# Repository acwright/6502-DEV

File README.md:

6502-DEV
========

An **AC6502** retro-style 8-bit computer based on the **65C02** microprocessor.

> 📖 **Guide:** [AC6502 Documentation](https://acwright.github.io/6502-DOCS/) — the user's and programmer's guide for the whole family.
> See [DEV's page in the family appendix](https://acwright.github.io/6502-DOCS/family/dev).

---

**Building one? Every part you need, with supplier numbers and known issues, is in [BOM.md](BOM.md).**

## Table of Contents

- [Overview](#overview)
- [Architecture](#architecture)
- [Systems](#systems)
- [Software](#software)
- [Hardware](#hardware)
  - [DEV Board](#dev-board)
  - [DEV Output Board](#dev-output-board)
- [Which revision to make](#which-revision-to-make)
- [Firmware](#firmware)
  - [DB Emulator](#db-emulator)
  - [DOB Display](#dob-display)
- [CAD](#cad)
- [Production](#production)
- [Schematics](#schematics)
- [Shared lines](#shared-lines)
- [Extra pins: `EXP0`–`EXP3` and `HRDB`](#extra-pins-exp0exp3-and-hrdb)
- [Jumpers](#jumpers)
- [Off-board headers](#off-board-headers)
- [Libraries](#libraries)
- [Bill of Materials](#bill-of-materials)
- [License](#license)

---

## Overview

The AC6502 ecosystem is a family of open-source, 65C02-based computers sharing a common architecture, memory map, and [BIOS](https://github.com/acwright/6502-BIOS). Each computer in the family is purpose-built for a different use case but runs the same software and firmware.

The **DEV** is an emulation-based development system. It replaces the physical 65C02 CPU with a [Teensy 4.1](https://www.pjrc.com/store/teensy41.html) running cycle-accurate 65C02 emulation via [vrEmu6502](https://github.com/visrealm/vrEmu6502).
## Architecture

All AC6502 computers share:

- **CPU**: 65C02 (or accurate emulation)
- **Memory**: 32KB RAM + 32KB ROM, with optional banked RAM expansion
- **Memory Map**: Standardized across the ecosystem — zero page, stack, I/O space ($8000–$9FFF), system ROM, and interrupt vectors at $FFFA–$FFFF
- **Bus**: 16-bit address bus, 8-bit bidirectional data bus, standard 65C02 control signals (RW, PHI2, RESET, IRQ, NMI, RDY, SYNC)
- **BIOS**: A common [BIOS](https://github.com/acwright/6502-BIOS) provides the kernel, monitor, and BASIC interpreter across all systems

## Systems

| Project | Description |
|---------|-------------|
| [6502-ACE](https://github.com/acwright/6502-ACE) | All-in-one Computer Experience — A single board computer |
| [6502-COB](https://github.com/acwright/6502-COB) | Computer On a Backplane — Modular desktop computer with expandable card slots |
| [6502-DEV](https://github.com/acwright/6502-DEV) | Development Environment Vehicle — Emulation-based dev system (YOU ARE HERE) |
| [6502-KIM](https://github.com/acwright/6502-KIM) | Keypad Input Monitor - KIM-1 inspired minimal computer |
| [6502-VCS](https://github.com/acwright/6502-VCS) | Video Computer System — Cartridge-based retro gaming console |

## Software

| Project | Description |
|---------|-------------|
| [6502-BIOS](https://github.com/acwright/6502-BIOS) | The shared BIOS (kernel, monitor, BASIC) for all AC6502 computers |
| [6502-EMULATOR](https://github.com/acwright/6502-EMULATOR) | Emulator for the whole family — desktop app, browser build, and a command line for scripted runs |
| [6502-PRG](https://github.com/acwright/6502-PRG) | Template project for writing assembly language programs |
| [6502-CRT](https://github.com/acwright/6502-CRT) | Template project for writing assembly language cartridges |
| [6502-ASM](https://github.com/acwright/6502-ASM) | Assembly language example programs and demos |
| [6502-BAS](https://github.com/acwright/6502-BAS) | BASIC program listings |
| [6502-WOZMON](https://github.com/acwright/6502-WOZMON) | Wozmon as a standalone ROM |
| [6502-NOP](https://github.com/acwright/6502-NOP) | An all-NOP ROM, for probing a board during bring-up |
| [6502-DOCS](https://github.com/acwright/6502-DOCS) | The documentation site — the guide, the printable reference cards, branding and label artwork |
| [cffs](https://github.com/acwright/cffs) | Builds CompactFlash disk images for the BIOS filesystem |
| [bastok](https://github.com/acwright/bastok) | Tokenizes BASIC listings into `.prg` images, and back |
| [bin2woz](https://github.com/acwright/bin2woz) | Converts a binary into a Wozmon serial upload |

## Hardware

This repository contains KiCad 7.0+ PCB designs for the two boards that make up the DEV system.

### DEV Board
`Hardware/DEV Board/`

The main board hosting the Teensy 4.1. Provides 65C02 bus emulation, SD card storage, Ethernet, USB keyboard/joystick input, and hardware control buttons (Run/Stop, Step, Reset, Frequency). Includes a bus connector and card slot with level shifters for optional real hardware expansion.

### DEV Output Board
`Hardware/DEV Output Board/`

The AV output board hosting a Teensy 4.0 and a 2.4" ILI9341 TFT LCD. Emulates a TMS9918A Video Display Processor and a MOS 6581 SID audio synthesizer, driven in real time via high-speed serial from the DEV Board. The DEV Board sends the same AV packets over USB at the same time, so a browser can render the output in parallel with this board — the two paths are simultaneous, not alternatives.

<!-- Which revision to make: generated by Tools/revision-audit/register.py from Tools/data/orders.json. Edit that file, not this section. -->
## Which revision to make

**Make the newest revision of a board, and check its label first.** The table below gives each board's newest revision. A newer revision fixes what was found on the older ones. Every revision, old and new, is in [REVISIONS.md](REVISIONS.md), with what changed in each.

Each revision carries one of three labels:

- **Tested:** This revision was built and tested.
- **Proven design:** Not built at this revision, but its circuit is a tested revision's. The only changes are silkscreen text, part values, mounting holes, outline clean-up, parts moved a fraction of a millimetre onto their grid, capacitor pitch, socket outlines, a footprint swap with the same holes, a solder jumper's default, the solder mask or paste at a card edge, or tracks rerouted or pours refilled with DRC and the netlist check passing. A builder can treat it as tested.
- **Untested:** The circuit, the power path or the layout changed in a way that only a built board proves, or the board has never been built at all.

[BOM.md](BOM.md) has the parts for every revision, and its known issues.

| Board | Newest revision | Label | Why |
|---|---|---|---|
| DEV Board | 1.1 | **Proven design** | Rev 1.0's circuit; the IC designators placed by the family's rule. |
| DEV Output Board | 1.1 | **Proven design** | Silkscreen text only. |
<!-- End of which revision to make -->

## Firmware

This repository contains [PlatformIO](https://platformio.org/)-based firmware for both boards.

### DB Emulator
`Firmware/DB Emulator/`

Firmware for the Teensy 4.1 on the DEV Board. Provides:

- Cycle-accurate 65C02 emulation
- SD card ROM/cartridge/program loading and memory snapshots
- Ethernet with mDNS (`6502.local`) and an embedded web control interface
- USB keyboard and joystick support (Xbox 360/One)
- AV packet output to both destinations at once — over USB to the browser (Web Serial API) and over hardware UART at 6 Mbps to the DOB Display
- Serial terminal interface (115200 baud)
- Hardware button control (Run/Stop, Step, Reset, Frequency)
- Variable CPU clock speed

See [Firmware/DB Emulator/README.md](./Firmware/DB%20Emulator/README.md) for setup and usage instructions.

### DOB Display
`Firmware/DOB Display/`

Firmware for the Teensy 4.0 on the DEV Output Board. Provides:

- TMS9918A VDP emulation (all four display modes, 256×192 active area)
- MOS 6581 SID audio emulation (3 voices, ADSR envelopes, PWM audio output)
- AV packet stream input at 6 Mbps over hardware UART from the DB Emulator (which also streams the same packets over USB to the browser)

See [Firmware/DOB Display/README.md](./Firmware/DOB%20Display/README.md) for setup and usage instructions.

## CAD
`CAD/`

3D-printable enclosure parts and laser-cut top panels for the DEV system.

**Board images** are in `CAD/Images/<Board>/Rev X/`: `Front.png` and `Back.png` on white, and `Front Transparent.png` and `Back Transparent.png` with no background. Every image is a 3D render at the same size, with the black solder mask and white silkscreen the boards are made with. Bare-board photos may differ, because the renders show parts fitted.

**Top panels are versioned by board revision**, like `Hardware/`: `CAD/Tops/<Board>/Rev X/`. Each revision has its own complete folder, even when two revisions share the same files. `Bases/` holds the parts for a whole computer, not for one board, so it isn't versioned.

The **[plate mounting drawing](CAD/Bases/Plate%20Mounting%20Drawing.png)** ([SVG](CAD/Bases/Plate%20Mounting%20Drawing.svg)) shows where the DEV Board and the DEV Output Board mount on the base plate, with every hole's position and the hardware the build needs. The plate is a stack of three 3 mm acrylic layers.

## Production
`Production/`

[REVISIONS.md](REVISIONS.md) lists every board revision: whether it was made, its JLCPCB order, the commit it was made from, and what fits it.

JLCPCB-ready Gerber files and BOM/CPL for PCB fabrication and assembly.

## Schematics
`Schematics/`

PDF schematics for each board.

## Shared lines

Five lines of the 6502 bus are shared by every board on it: `RESB`, `IRQB`, `NMIB`, `RDY` and `BE`. A board may pull one of these lines low, and nothing drives one high. Each line is held high by one 10kΩ pull-up resistor to VCC, on the board with the CPU: the ACE Board, the KIM Board, the VCS Main Board, the COB CPU Card or CPU Card Pro, or the DEV Board. No other board has one. Two pull-ups on the same line would sit in parallel and lower its resistance, so a card that adds its own pull-up changes the machine for every other board. The VIAs and PIAs in the BOMs, the W65C22N and W65C21N, have open-drain interrupt outputs for this reason.

**Interrupt outputs.** Whatever drives `IRQB` or `NMIB` may only pull it low. Every board is drawn for the parts in its BOM and works as shipped, with no jumper to cut or bridge:

- **A part whose interrupt output is open-drain** (the W65C22N, W65C21N, R6551AP, DS1511Y and TMS9918A) drives the line directly, or through a diode with a solder jumper across it that ships bridged. The diode is fitted either way. To use a part that drives its interrupt high as well as low instead, such as a W65C22S or a replacement of your own, cut the jumper: the diode then lets the part only pull the line low. A board with no diode in the line can't take such a part.
- **A part that drives its interrupt high as well as low** (the pico9918, the VERA module, and a microcontroller such as the ATmega1284 or a Raspberry Pi Pico) reaches the line through a diode, a BAT85 or a 1N914, with its cathode toward the part. Where a solder jumper sits across that diode, it ships open. The diode is then the only path to the line, so fit it, and never bridge the jumper, because the part would then hold the line high against every other interrupt source.
- **A microcontroller wired to the line directly,** as on the ACE Board, the Mega Helper and the Flash Helper, drives it open-drain in its firmware: it sets the pin low or leaves it as an input, and never drives it high.

The *Jumpers* section below gives each board's interrupt jumper.

The same holds where a board has its own reset circuit. A reset switch, its timer and the transistor that pulls `RESB` low can be on any board, such as the COB Backplane Pro or the Clock Card, but the `RESB` pull-up is only ever on the board with the CPU. Each of those boards draws its pull-ups together, in one group on its schematic.

The DEV Board is the exception on `RESB`. It stands in for a Main Board, so it owns reset: its Reset button goes to the Teensy, and the Teensy drives `RESB` onto the bus through U3, a level shifter that only sends signals out, as it drives `PHI2`. U3 holds `RESB` high or low, so the DEV Board has no `RESB` pull-up, and nothing else on its bus may pull `RESB` low. Connect a DEV only to a passive backplane, never to the COB Backplane Pro, whose reset circuit would pull against U3, and don't fit a card that pulls `RESB` low, such as the COB RTC Card.

`SOB` is a CPU pin that isn't on the bus. It is tied to VCC, directly or through a 10kΩ resistor.

A few chips have a pull-up of their own inside the chip, such as an ATmega's reset pin. Where such a pin is wired to `RESB`, its pull-up of 30–60kΩ sits in parallel with the 10kΩ one. That's harmless, because whatever pulls `RESB` low can sink the extra current many times over.

A revision that doesn't follow this yet says so in its known issues in [BOM.md](BOM.md), with what to fit or remove.

## Extra pins: `EXP0`–`EXP3` and `HRDB`

`EXP` stands for "extra pin". Four pins of the 6502 bus are left for a builder's own use: pin 4 is `EXP1`, pin 6 is `EXP0`, pin 19 is `EXP3` and pin 21 is `EXP2`.

Pins 4 and 6 have a second job. A cartridge ties both of them to GND. That pulls `HRDB` ("High ROM disable bar", active low) low on the board with the ROM, which takes `$C000–$FFFF` away from the ROM so that the cartridge answers there instead. So in a build that uses cartridges, pins 4 and 6 are reserved for `HRDB`, and nothing else may drive them. They are free as `EXP1` and `EXP0` only in a build that never uses cartridges. `EXP2` and `EXP3` are always free.

How the boards treat pins 4 and 6:

- **The ACE Board and the KIM Board** join them to their ROM's `HRDB` input, and their silk says `HRDB`. The VCS Main Board joins them the same way from Rev 1.1.
- **The COB Memory Card** joins them to its `HRDB` only through jumpers: fit two shunts on J2, or bridge JP1 and JP2, in a COB that takes cartridges. It is the only board with these jumpers, because the COB is the experimenter's build. The VCS Main Board Rev 1.0 had them too (J5, or JP3 and JP4); fit them, because the VCS always takes cartridges.
- **A cartridge** (the ROM Cart, the Flash Cart, the KIM Keypad Card) ties them to GND.
- **A board that only carries the bus through**, such as a backplane or a helper, calls them `EXP1` and `EXP0`, as its silk does, and a note on its schematic says what they carry.

<!-- Jumpers: generated by Tools/jumpers/gen.py from Tools/data/jumpers.json. Edit that file, not this section. -->
## Jumpers

None of this repository's boards has a jumper.

<!-- End of jumpers -->

<!-- Off-board headers: generated by Tools/offboard/gen.py from Tools/offboard/offboard.json, Tools/data/offboard.json and the PCB files. Edit those, not this section. -->
## Off-board headers

Some boards have small headers, such as `RESET SW`, `CLOCK ENBL SW`, `POWER LED` and `VCC`, that a standard build leaves empty. They are for a machine built into a full enclosure, which AC6502 doesn't offer today. In such a build, the parts a person handles are mounted on the case and wired to the board through these headers: the power jack, the switches, the LEDs and the keyboard. The matching parts on the board are then left off. For example, an ACE Board can sit inside a case with its power jack, power switch and key switches left off, and a Keyboard Helper as its keyboard.

To build a board for a case:

1. Fit the header, and wire the part on the case to it. The table says what goes on each pin.
2. Leave off the parts on the board that the table names. A button on the case can work beside the board's own button, but some parts, such as an LED that shares the board's resistor, can't share.
3. Set any jumper the table mentions. The [Jumpers](#jumpers) section has the rest.

The connector follows the kind of build. A single-board machine, the ACE Board or the KIM Board, uses plain 2.54 mm pin headers, which are simpler and cheaper. A board in a multi-board machine, every COB board and the separate boards of the VCS, the DEV and the KIM, uses JST XH, the family's standard for these headers.

The table lists every off-board header on each board's newest revision, read from the board's PCB file.

| Board | Rev | Header | Label | Connector | What it's for | Leave off |
|---|---|---|---|---|---|---|
| DEV Board | 1.1 | J3 | `PANEL` | Pin header, 2×4, 2.54 mm | Four buttons on the case, each between its pin and ground: Run/Stop on pin 1, Step on pin 3, Clock on pin 5 and Reset on pin 7. Pins 2, 4, 6 and 8 are ground. Each button is wired across one of SW1–SW4, the board's own buttons. | SW1–SW4, if the case covers them. Both sets of buttons work if they stay. |

<!-- End of off-board headers -->

## Libraries
`Libraries/`

Shared KiCad symbol and footprint libraries used across all AC6502 hardware projects, with their 3D models in `Models/`. A part is named for what it is and its shape, such as `RJ45 Jack LED` or `CR2032 Holder`, never for a manufacturer's part number, so a replacement part with the same footprint fits without renaming anything. The part numbers to buy are in [BOM.md](BOM.md). Every AC6502 repository carries the same copy of each part.

## Bill of Materials

Every part for every board, by revision, is in **[BOM.md](BOM.md)**, with supplier numbers, known issues, build notes and files to upload to Digi-Key and Mouser. What changed in each revision, and what is known about each one, is in **[REVISIONS.md](REVISIONS.md)**.

## License

Hardware designs are released under the [CERN Open Hardware Licence Version 2 – Permissive](https://ohwr.org/cern_ohl_p_v2.txt).  
Firmware is released under the MIT License — [DB Emulator](./Firmware/DB%20Emulator/LICENSE), [DOB Display](./Firmware/DOB%20Display/LICENSE).

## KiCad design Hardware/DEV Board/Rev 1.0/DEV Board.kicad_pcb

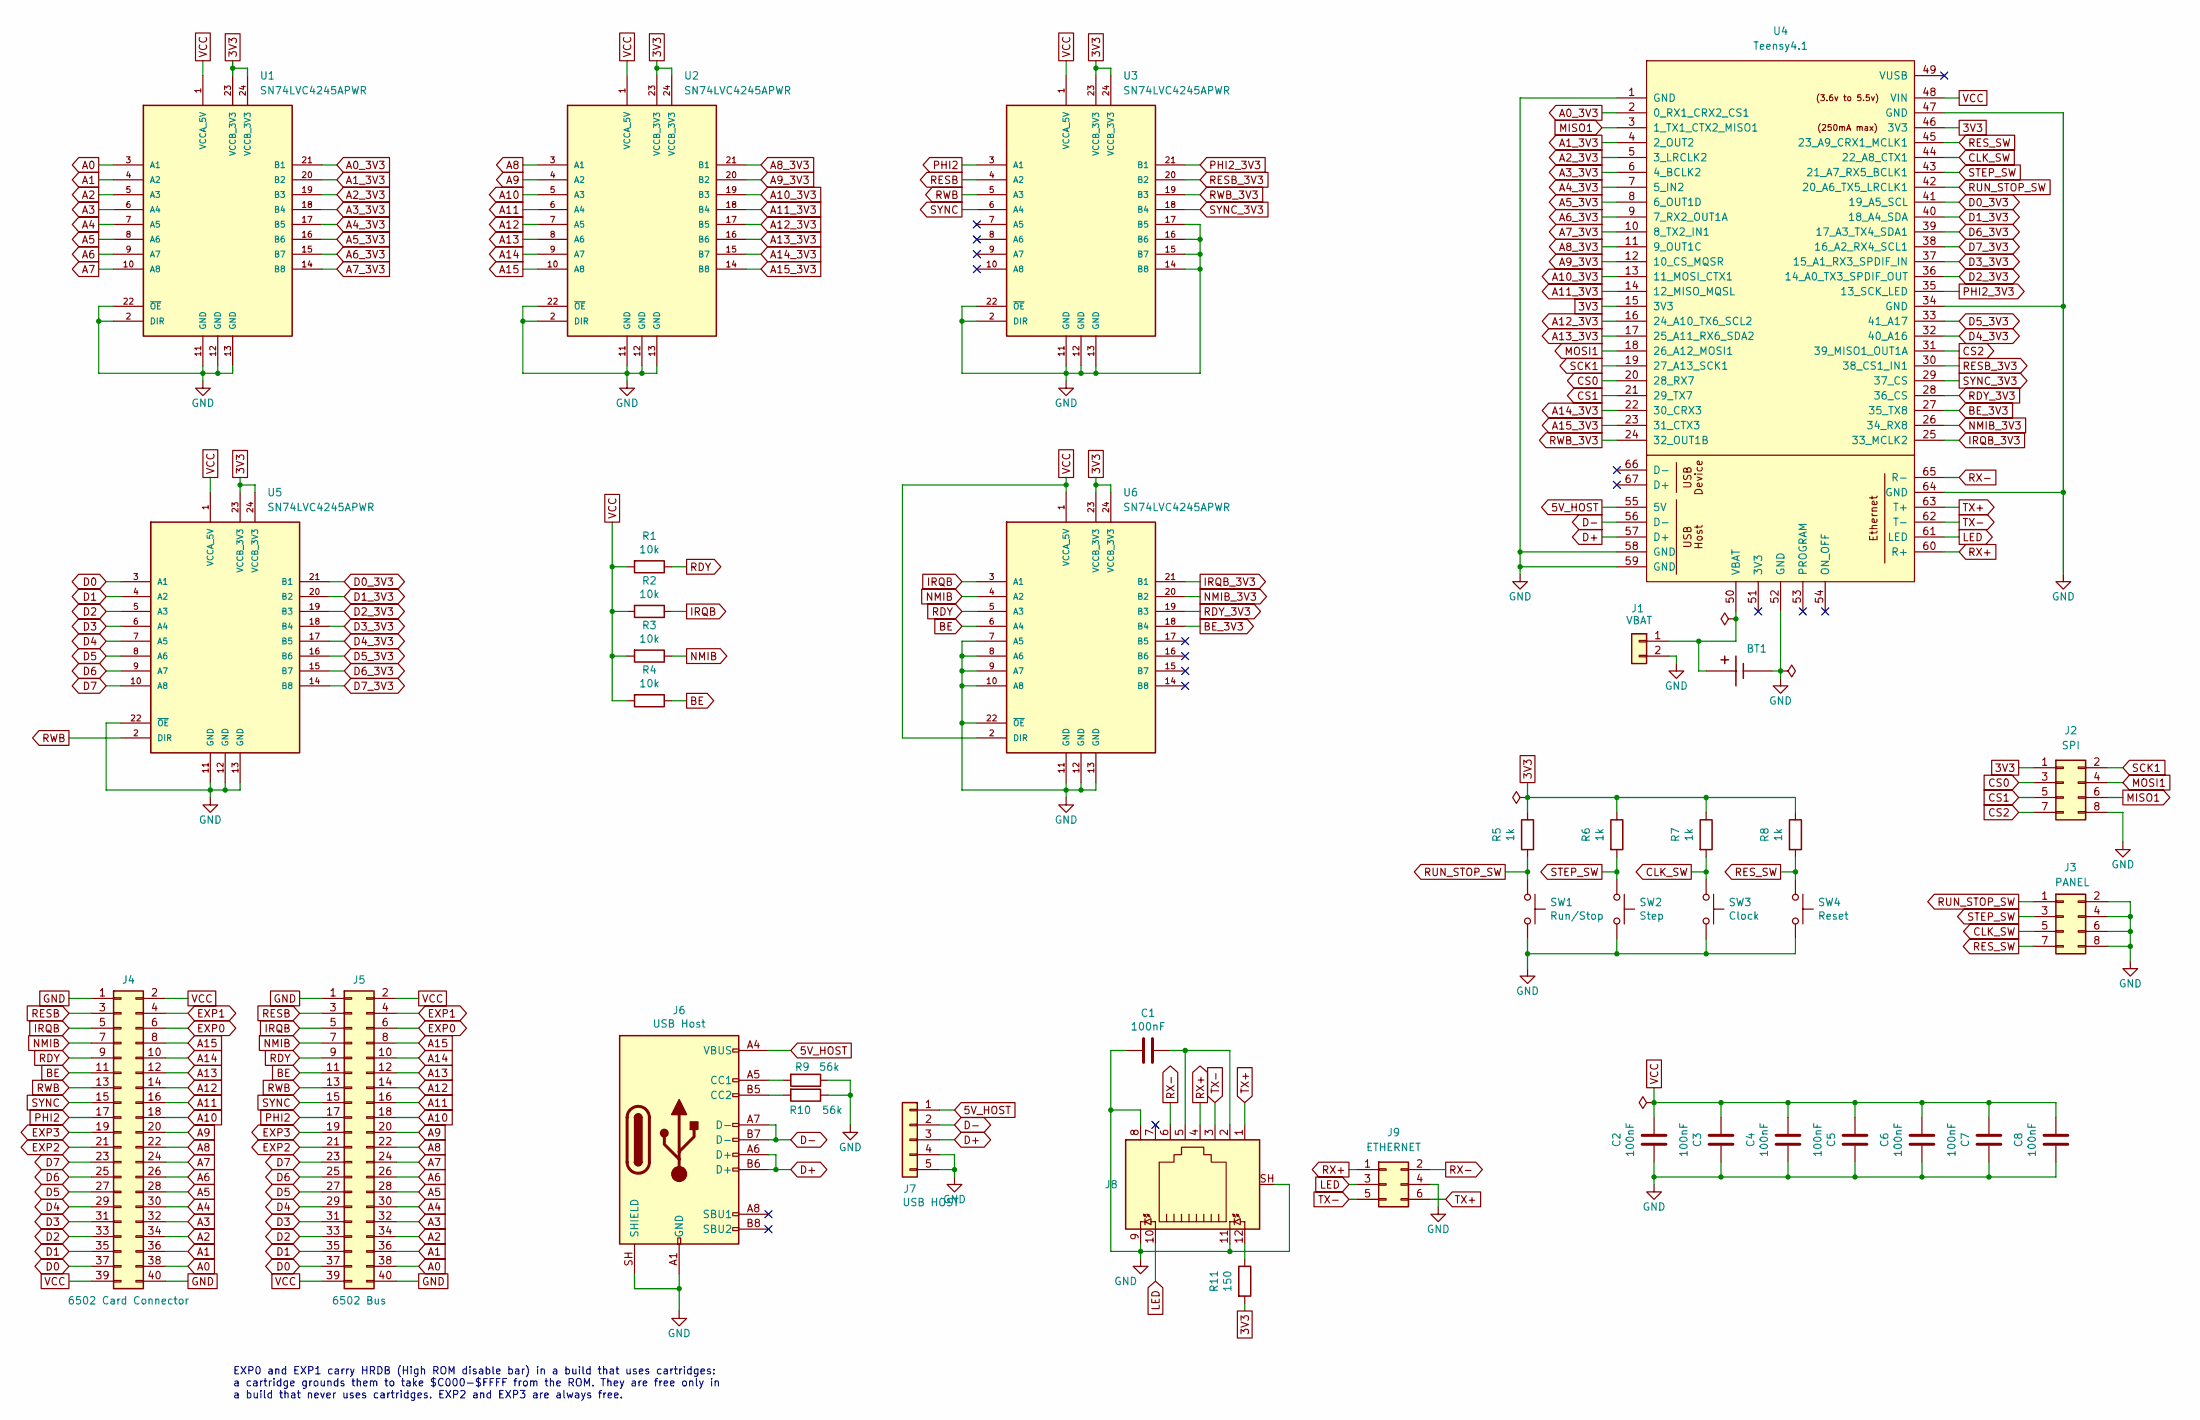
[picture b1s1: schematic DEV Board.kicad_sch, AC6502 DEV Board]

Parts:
BT1: CR2032; CR2032 Holder; Digikey 343-BAT-HLD-001-THM-TRCT-ND
C1, C2, C3, C4, C5, C6, C7, C8: 100nF; C_0805_2012Metric; LCSC C49678
J1: VBAT; PinHeader_1x02_P2.54mm_Vertical; Digikey S1011EC-40-ND
J2: SPI; PinHeader_2x04_P2.54mm_Vertical; Digikey S2011EC-40-ND
J3: PANEL; PinHeader_2x04_P2.54mm_Vertical; Digikey S2011EC-40-ND
J4: 6502 Card Connector; 6502 Card Slot; Digikey A31723-ND
J5: 6502 Bus; 6502 Bus Connector; Digikey 732-5401-ND
J6: USB Host; USB_C_Receptacle_HRO_TYPE-C-31-M-12; LCSC C2988369
J7: USB HOST; PinHeader_1x05_P2.54mm_Vertical; Digikey S1011EC-40-ND
J8: RJ45_LED; RJ45 Jack LED; Digikey 931-TMJDD111B083FC2A1D-ND
J9: ETHERNET; PinHeader_2x03_P2.00mm_Vertical; Digikey 2057-2PH2-06-UA-ND
R1, R2, R3, R4: 10k; R_0805_2012Metric; LCSC C17414
R5, R6, R7, R8: 1k; R_0805_2012Metric; LCSC C17513
R9, R10: 56k; R_0805_2012Metric; LCSC C169923
R11: 150; R_0805_2012Metric; LCSC C17471
SW1: Run/Stop; Tact Switch SMD 5.1mm; LCSC C318884
SW2: Step; Tact Switch SMD 5.1mm; LCSC C318884
SW3: Clock; Tact Switch SMD 5.1mm; LCSC C318884
SW4: Reset; Tact Switch SMD 5.1mm; LCSC C318884
U1, U2, U3, U5, U6: SN74LVC4245APWR; TSSOP-24_4.4x7.8mm_P0.65mm; LCSC C7859
U4: Teensy4.1; Teensy41

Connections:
3V3: J2.1, R5.1, R6.1, R7.1, R8.1, R11.2, U1.23 (VCCB_3V3), U1.24 (VCCB_3V3), U2.23 (VCCB_3V3), U2.24 (VCCB_3V3), U3.23 (VCCB_3V3), U3.24 (VCCB_3V3), U4.15 (3V3), U4.46 (3V3), U5.23 (VCCB_3V3), U5.24 (VCCB_3V3), U6.23 (VCCB_3V3), U6.24 (VCCB_3V3)
5V_HOST: J6.A4 (VBUS), J6.A9 (VBUS), J6.B4 (VBUS), J6.B9 (VBUS), J7.1, U4.55 (5V)
A0: J4.38, J5.38, U1.3 (A1)
A0_3V3: U1.21 (B1), U4.2 (0_RX1_CRX2_CS1)
A1: J4.36, J5.36, U1.4 (A2)
A1_3V3: U1.20 (B2), U4.4 (2_OUT2)
A2: J4.34, J5.34, U1.5 (A3)
A2_3V3: U1.19 (B3), U4.5 (3_LRCLK2)
A3: J4.32, J5.32, U1.6 (A4)
A3_3V3: U1.18 (B4), U4.6 (4_BCLK2)
A4: J4.30, J5.30, U1.7 (A5)
A4_3V3: U1.17 (B5), U4.7 (5_IN2)
A5: J4.28, J5.28, U1.8 (A6)
A5_3V3: U1.16 (B6), U4.8 (6_OUT1D)
A6: J4.26, J5.26, U1.9 (A7)
A6_3V3: U1.15 (B7), U4.9 (7_RX2_OUT1A)
A7: J4.24, J5.24, U1.10 (A8)
A7_3V3: U1.14 (B8), U4.10 (8_TX2_IN1)
A8: J4.22, J5.22, U2.3 (A1)
A8_3V3: U2.21 (B1), U4.11 (9_OUT1C)
A9: J4.20, J5.20, U2.4 (A2)
A9_3V3: U2.20 (B2), U4.12 (10_CS_MQSR)
A10: J4.18, J5.18, U2.5 (A3)
A10_3V3: U2.19 (B3), U4.13 (11_MOSI_CTX1)
A11: J4.16, J5.16, U2.6 (A4)
A11_3V3: U2.18 (B4), U4.14 (12_MISO_MQSL)
A12: J4.14, J5.14, U2.7 (A5)
A12_3V3: U2.17 (B5), U4.16 (24_A10_TX6_SCL2)
A13: J4.12, J5.12, U2.8 (A6)
A13_3V3: U2.16 (B6), U4.17 (25_A11_RX6_SDA2)
A14: J4.10, J5.10, U2.9 (A7)
A14_3V3: U2.15 (B7), U4.22 (30_CRX3)
A15: J4.8, J5.8, U2.10 (A8)
A15_3V3: U2.14 (B8), U4.23 (31_CTX3)
BE: J4.11, J5.11, R4.1, U6.6 (A4)
BE_3V3: U4.27 (35_TX8), U6.18 (B4)
CLK_SW: J3.5, R7.2, SW3.1, U4.44 (22_A8_CTX1)
CS0: J2.3, U4.20 (28_RX7)
CS1: J2.5, U4.21 (29_TX7)
CS2: J2.7, U4.31 (39_MISO1_OUT1A)
D0: J4.37, J5.37, U5.3 (A1)
D0_3V3: U4.41 (19_A5_SCL), U5.21 (B1)
D1: J4.35, J5.35, U5.4 (A2)
D1_3V3: U4.40 (18_A4_SDA), U5.20 (B2)
D2: J4.33, J5.33, U5.5 (A3)
D2_3V3: U4.36 (14_A0_TX3_SPDIF_OUT), U5.19 (B3)
D3: J4.31, J5.31, U5.6 (A4)
D3_3V3: U4.37 (15_A1_RX3_SPDIF_IN), U5.18 (B4)
D4: J4.29, J5.29, U5.7 (A5)
D4_3V3: U4.32 (40_A16), U5.17 (B5)
D5: J4.27, J5.27, U5.8 (A6)
D5_3V3: U4.33 (41_A17), U5.16 (B6)
D6: J4.25, J5.25, U5.9 (A7)
D6_3V3: U4.39 (17_A3_TX4_SDA1), U5.15 (B7)
D7: J4.23, J5.23, U5.10 (A8)
D7_3V3: U4.38 (16_A2_RX4_SCL1), U5.14 (B8)
D+: J6.A6 (D+), J6.B6 (D+), J7.3, U4.57 (D+)
D-: J6.A7 (D-), J6.B7 (D-), J7.2, U4.56 (D-)
EXP0: J4.6, J5.6
EXP1: J4.4, J5.4
EXP2: J4.21, J5.21
EXP3: J4.19, J5.19
GND: BT1.-, C1.2, C2.2, C3.1, C4.2, C5.1, C6.2, C7.1, C8.2, J1.2, J2.8, J3.2, J3.4, J3.6, J3.8, J4.1, J4.40, J5.1, J5.40, J6.A1 (GND), J6.A12 (GND), J6.B1 (GND), J6.B12 (GND), J6.S1 (SHIELD), J6.SH (SHIELD), J7.4, J7.5, J8.8, J8.9, J8.11, J8.SH, J9.4, R9.1, R10.1, SW1.2, SW2.2, SW3.2, SW4.2, U1.2 (DIR), U1.11 (GND), U1.12 (GND), U1.13 (GND), U1.22 (~OE), U2.2 (DIR), U2.11 (GND), U2.12 (GND), U2.13 (GND), U2.22 (~OE), U3.2 (DIR), U3.11 (GND), U3.12 (GND), U3.13 (GND), U3.14 (B8), U3.15 (B7), U3.16 (B6), U3.17 (B5), U3.22 (~OE), U4.1 (GND), U4.34 (GND), U4.47 (GND), U4.52 (GND), U4.58 (GND), U4.59 (GND), U4.64 (GND), U5.11 (GND), U5.12 (GND), U5.13 (GND), U5.22 (~OE), U6.7 (A5), U6.8 (A6), U6.9 (A7), U6.10 (A8), U6.11 (GND), U6.12 (GND), U6.13 (GND), U6.22 (~OE)
IRQB: J4.5, J5.5, R2.1, U6.3 (A1)
IRQB_3V3: U4.25 (33_MCLK2), U6.21 (B1)
LED: J8.10, J9.3, U4.61 (LED)
MISO1: J2.6, U4.3 (1_TX1_CTX2_MISO1)
MOSI1: J2.4, U4.18 (26_A12_MOSI1)
NMIB: J4.7, J5.7, R3.1, U6.4 (A2)
NMIB_3V3: U4.26 (34_RX8), U6.20 (B2)
unnamed: C1.1, J8.2, J8.5
unnamed: BT1.+, J1.1, U4.50 (VBAT)
unnamed: J6.A5 (CC1), R9.2
unnamed: J6.B5 (CC2), R10.2
unnamed: J8.12, R11.1
PHI2: J4.17, J5.17, U3.3 (A1)
PHI2_3V3: U3.21 (B1), U4.35 (13_SCK_LED)
RDY: J4.9, J5.9, R1.1, U6.5 (A3)
RDY_3V3: U4.28 (36_CS), U6.19 (B3)
RESB: J4.3, J5.3, U3.4 (A2)
RESB_3V3: U3.20 (B2), U4.30 (38_CS1_IN1)
RES_SW: J3.7, R8.2, SW4.1, U4.45 (23_A9_CRX1_MCLK1)
RUN_STOP_SW: J3.1, R5.2, SW1.1, U4.42 (20_A6_TX5_LRCLK1)
RWB: J4.13, J5.13, U3.5 (A3), U5.2 (DIR)
RWB_3V3: U3.19 (B3), U4.24 (32_OUT1B)
RX+: J8.4, J9.1, U4.60 (R+)
RX-: J8.6, J9.2, U4.65 (R-)
SCK1: J2.2, U4.19 (27_A13_SCK1)
STEP_SW: J3.3, R6.2, SW2.1, U4.43 (21_A7_RX5_BCLK1)
SYNC: J4.15, J5.15, U3.6 (A4)
SYNC_3V3: U3.18 (B4), U4.29 (37_CS)
TX+: J8.1, J9.6, U4.63 (T+)
TX-: J8.3, J9.5, U4.62 (T-)
VCC: C2.1, C3.2, C4.1, C5.2, C6.1, C7.2, C8.1, J4.2, J4.39, J5.2, J5.39, R1.2, R2.2, R3.2, R4.2, U1.1 (VCCA_5V), U2.1 (VCCA_5V), U3.1 (VCCA_5V), U4.48 (VIN), U5.1 (VCCA_5V), U6.1 (VCCA_5V), U6.2 (DIR)

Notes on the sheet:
EXP0 and EXP1 carry HRDB (High ROM disable bar) in a build that uses cartridges: a cartridge grounds them to take $C000-$FFFF from the ROM. They are free only in a build that never uses cartridges. EXP2 and EXP3 are always free.

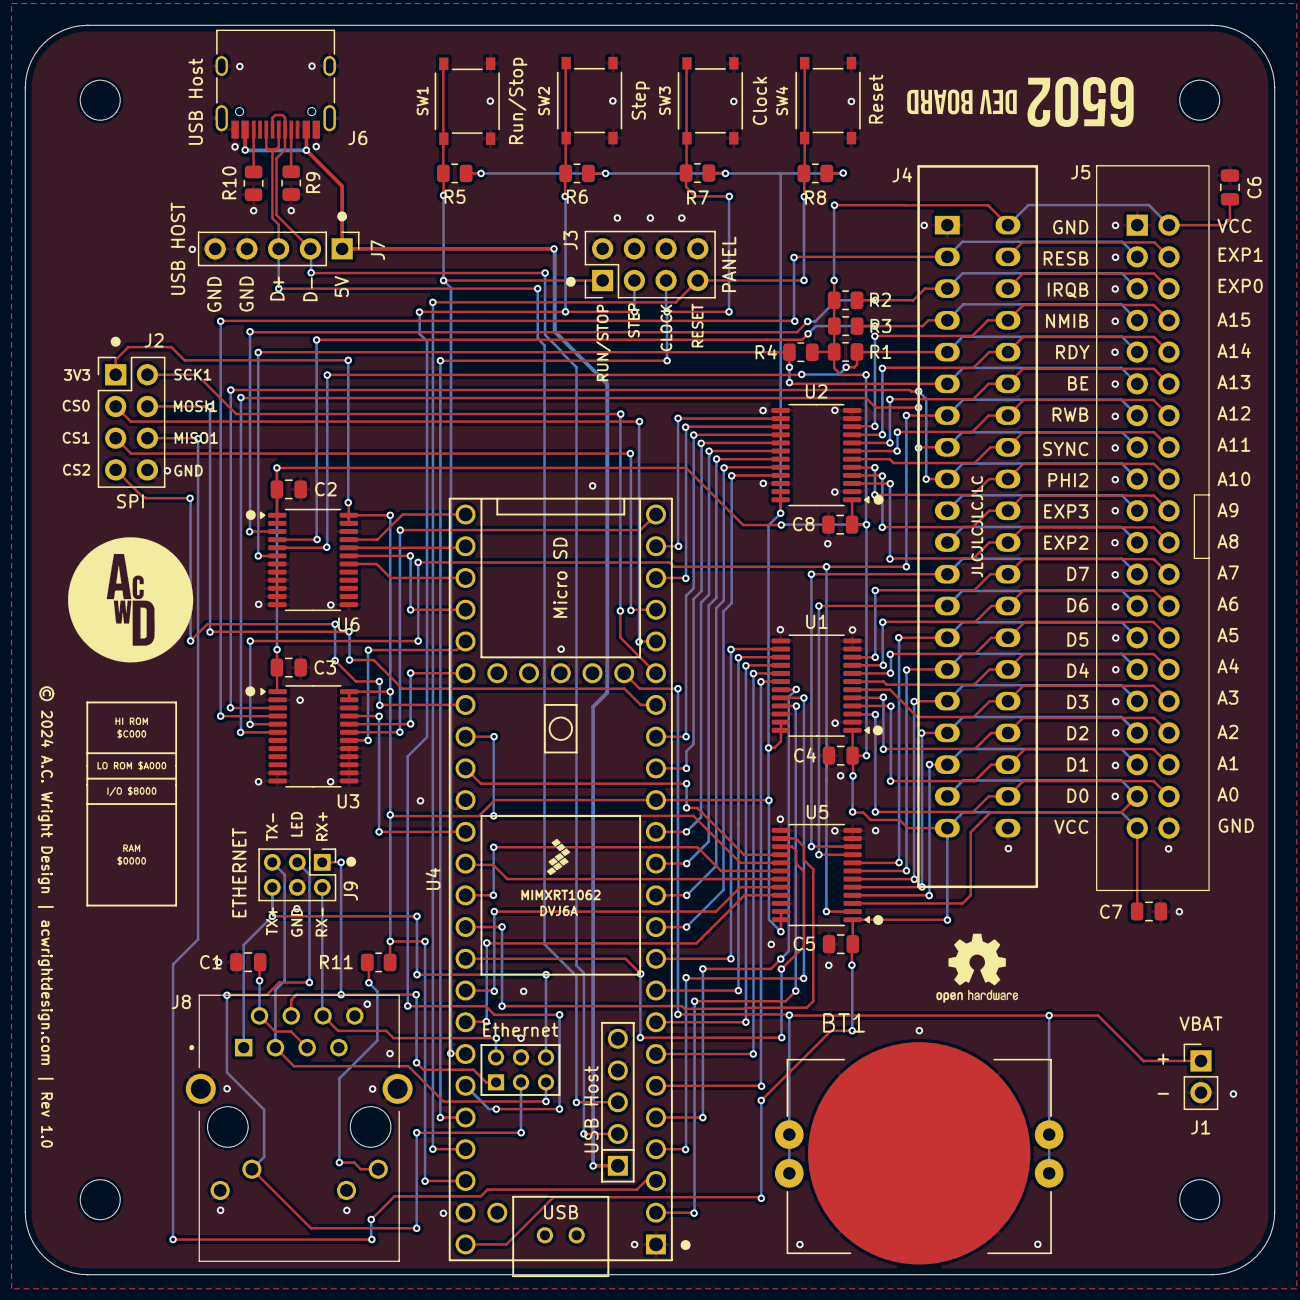
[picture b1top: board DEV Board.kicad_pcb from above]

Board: 2 copper layers, 100.0 x 100.0 mm, 43 parts (0 on the bottom side), 94 nets.

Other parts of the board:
H1, H2, H3, H4: MountingHole; MountingHole_3.2mm_M3

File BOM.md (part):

# Bill of materials: 6502-DEV

Every part for every board in this repository, by revision, with supplier numbers.

## How to use this

1. **Find your board and revision** in [Which revision do I have?](#which-revision-do-i-have)
2. **Read the [known issues](#known-issues)** for that revision, because they change what you buy or fit.
3. **Order from the table for your revision.** Each revision links to files you can upload to Digi-Key and Mouser. Those files are for one board, so multiply the quantities if you're building more. If a site asks which column is which, the first column is its part number and the third is the quantity. A cart only holds what that supplier sells, so check the table for anything else, such as chips from Jameco.
4. **Set the jumpers** before the first power-up. The README's [Jumpers](README.md#jumpers) section says which ones each board needs, and the table for your revision lists the shunts.

**Pre-soldered parts.** Some boards on Tindie come with their surface-mount parts already soldered. Parts marked **Yes** under Pre-soldered are the ones soldered on those boards. Check your listing, because others are sold as a bare PCB. Each revision that has such parts also has a `through-hole` cart that leaves them out. To solder a bare board yourself, use the full cart.

**Suppliers.** Every part has one set of numbers, so the same resistor is the same order line on every board. The numbers were read from Digi-Key and Mouser on 2026-11-04, and stock changes. A blank supplier cell means that supplier doesn't sell the part, or only sells it in bulk.

**The `bom.csv` files** under `Production/` are for JLCPCB assembly. They list the same parts. A blank LCSC cell there means JLCPCB doesn't place that part, and JLCPCB's "missing parts" warning about it is expected.

## Which revision do I have?

Look on the board: the silk prints the revision next to the copyright line. [REVISIONS.md](REVISIONS.md) has the facts for each one, and its history lists what changed between them.

**To make a new board, make the newest revision**, and check its label first. The README's [Which revision to make](README.md#which-revision-to-make) explains the three labels: **Tested**, **Proven design** and **Untested**.

| Board | Revision | What the silk says | Status | Label |
|---|---|---|---|---|
| [DEV Board](#dev-board) | 1.0 | Rev 1.0 | Made, tested | **Tested** |
| [DEV Board](#dev-board) | 1.1 | Rev 1.1 | Drawn, not made yet | **Proven design**: rev 1.0's circuit; the IC designators placed by the family's rule |
| [DEV Output Board](#dev-output-board) | 1.0 | Rev 1.0 | Made, tested | **Tested** |
| [DEV Output Board](#dev-output-board) | 1.1 | Rev 1.1 | Drawn, not made yet | **Proven design**: silkscreen text only |

## Known issues

These change what you buy or fit. The boards themselves stay as they were made.

| Board | Revision | Parts | Issue |
|---|---|---|---|
| DEV Board | 1.0 | R1–R4 | Fit 10k, not 1k. If your board came with 1k soldered here, replace it. See the build notes. |
| DEV Board | 1.0 | BT1 | `BAT-HLD-001-THM`, on the tested boards, is obsolete. `BAT-HLD-001-THM-TR` is its listed continuation, with no stock today and no board built with it yet. |
| DEV Board | 1.1 | BT1 | `BAT-HLD-001-THM`, on the tested boards, is obsolete. `BAT-HLD-001-THM-TR` is its listed continuation, with no stock today and no board built with it yet. |

### Build notes

How to build each board, where it needs more than its parts list.

<!-- Build notes: hand-written. Tools/bom/gen_bom.py keeps everything between these two markers. -->

**DEV Board**

**Rev 1.0's limits:**
- **Pull-ups:** fit 10kΩ for R1–R4, as the parts list says. Rev 1.0 was first drawn with 1kΩ there, and its files have said 10kΩ since 2026-11-04. With a 1kΩ pull-up, a device that pulls `IRQB` low sinks 5 mA, more than the 3.2 mA that the W65C22's and W65C21's IRQ outputs are rated for.

**Building a Rev 1.0:** nothing to do. Rev 1.1 changes only where two designators sit on the silkscreen.

**What it connects to:**
- **`RESB`:** the DEV Board stands in for a Main Board, so it owns reset. The Teensy drives `RESB` onto the bus through U3, a level shifter that only sends signals out, so there's no `RESB` pull-up, and nothing else may pull `RESB` low. Connect a DEV only to a passive backplane, never to the COB Backplane Pro, whose reset circuit would pull against U3, and don't fit a card that pulls `RESB` low, such as the COB RTC Card.

<!-- End of build notes. -->

## DEV Board

### DEV Board Rev 1.1

Drawn, not made yet. **Proven design**: rev 1.0's circuit; the IC designators placed by the family's rule.

Cart files: [digikey.csv](BOM/DEV%20Board/Rev%201.1/digikey.csv), [mouser.csv](BOM/DEV%20Board/Rev%201.1/mouser.csv), [digikey-through-hole.csv](BOM/DEV%20Board/Rev%201.1/digikey-through-hole.csv), [mouser-through-hole.csv](BOM/DEV%20Board/Rev%201.1/mouser-through-hole.csv)

| Reference | Qty | Value | Part | Digi-Key | Mouser | Other | Pre-soldered |
|---|---|---|---|---|---|---|---|
| BT1 | 1 | CR2032 | TE Connectivity Linx BAT-HLD-001-THM-TR | [343-BAT-HLD-001-THM-TRCT-ND](https://www.digikey.com/en/products/filter?keywords=343-BAT-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 |  |  | |
| C1–C8 | 8 | 100nF | YAGEO CC0805KRX7R9BB104 | [311-1140-1-ND](https://www.digikey.com/en/products/filter?keywords=311-1140-1-ND) | [603-CC805KRX7R9BB104](https://www.mouser.com/ProductDetail/603-CC805KRX7R9BB104) | LCSC [C49678](https://www.lcsc.com/search?q=C49678) | Yes |
| J1 | 1 | VBAT | Pin header 1×2, 2.54 mm, cut from a strip | [S1011EC-40-ND](https://www.digikey.com/en/products/filter?keywords=S1011EC-40-ND) | [200-TSW14007TS](https://www.mouser.com/ProductDetail/200-TSW14007TS) |  | |
| J2 | 1 | SPI | Pin header 2×4, 2.54 mm, cut from a strip | [S2011EC-40-ND](https://www.digikey.com/en/products/filter?keywords=S2011EC-40-ND) | [649-67996-140HLF](https://www.mouser.com/ProductDetail/649-67996-140HLF) |  | |
| J3 | 1 | PANEL | Pin header 2×4, 2.54 mm, cut from a strip | [S2011EC-40-ND](https://www.digikey.com/en/products/filter?keywords=S2011EC-40-ND) | [649-67996-140HLF](https://www.mouser.com/ProductDetail/649-67996-140HLF) |  | |
| J4 | 1 | 6502 Card Connector | TE Connectivity 5-5530843-4 | [A31723-ND](https://www.digikey.com/en/products/filter?keywords=A31723-ND) | [571-5-5530843-4](https://www.mouser.com/ProductDetail/571-5-5530843-4) |  | |
| J5 | 1 | 6502 Bus | Würth Elektronik 61204021621 | [732-5401-ND](https://www.digikey.com/en/products/filter?keywords=732-5401-ND) | [710-61204021621](https://www.mouser.com/ProductDetail/710-61204021621) |  | |
| J6 | 1 | USB Host | G-Switch GT-USB-7010ASV |  |  | LCSC [C2988369](https://www.lcsc.com/search?q=C2988369) | Yes |
| J7 | 1 | USB HOST | Pin header 1×5, 2.54 mm, cut from a strip | [S1011EC-40-ND](https://www.digikey.com/en/products/filter?keywords=S1011EC-40-ND) | [200-TSW14007TS](https://www.mouser.com/ProductDetail/200-TSW14007TS) |  | |
| J8 | 1 | RJ45_LED | Taoglas TMJDD111B083FC2A1D | [931-TMJDD111B083FC2A1D-ND](https://www.digikey.com/en/products/filter?keywords=931-TMJD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 | [960-TDD111B083FC2A1D](https://www.mouser.com/ProductDetail/960-TDD111B083FC2A1D) |  | |
| J9 | 1 | ETHERNET | Adam Tech 2PH2-06-UA | [2057-2PH2-06-UA-ND](https://www.digikey.com/en/products/filter?keywords=2057-2PH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 | [200-TMM10301TD](https://www.mouser.com/ProductDetail/200-TMM10301TD) |  | |
| R1–R4 | 4 | 10k | YAGEO RC0805FR-0710KL | [311-10.0KCRCT-ND](https://www.digikey.com/en/products/filter?keywords=311-10.0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 | [603-RC0805FR-0710KL](https://www.mouser.com/ProductDetail/603-RC0805FR-0710KL) | LCSC [C17414](https://www.lcsc.com/search?q=C17414) | Yes |
| R5–R8 | 4 | 1k | YAGEO RC0805FR-071KL | [311-1.00KCRCT-ND](https://www.digikey.com/en/products/filter?keywords=311-1.00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 | [603-RC0805FR-071KL](https://www.mouser.com/ProductDetail/603-RC0805FR-071KL) | LCSC [C17513](https://www.lcsc.com/search?q=C17513) | Yes |
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
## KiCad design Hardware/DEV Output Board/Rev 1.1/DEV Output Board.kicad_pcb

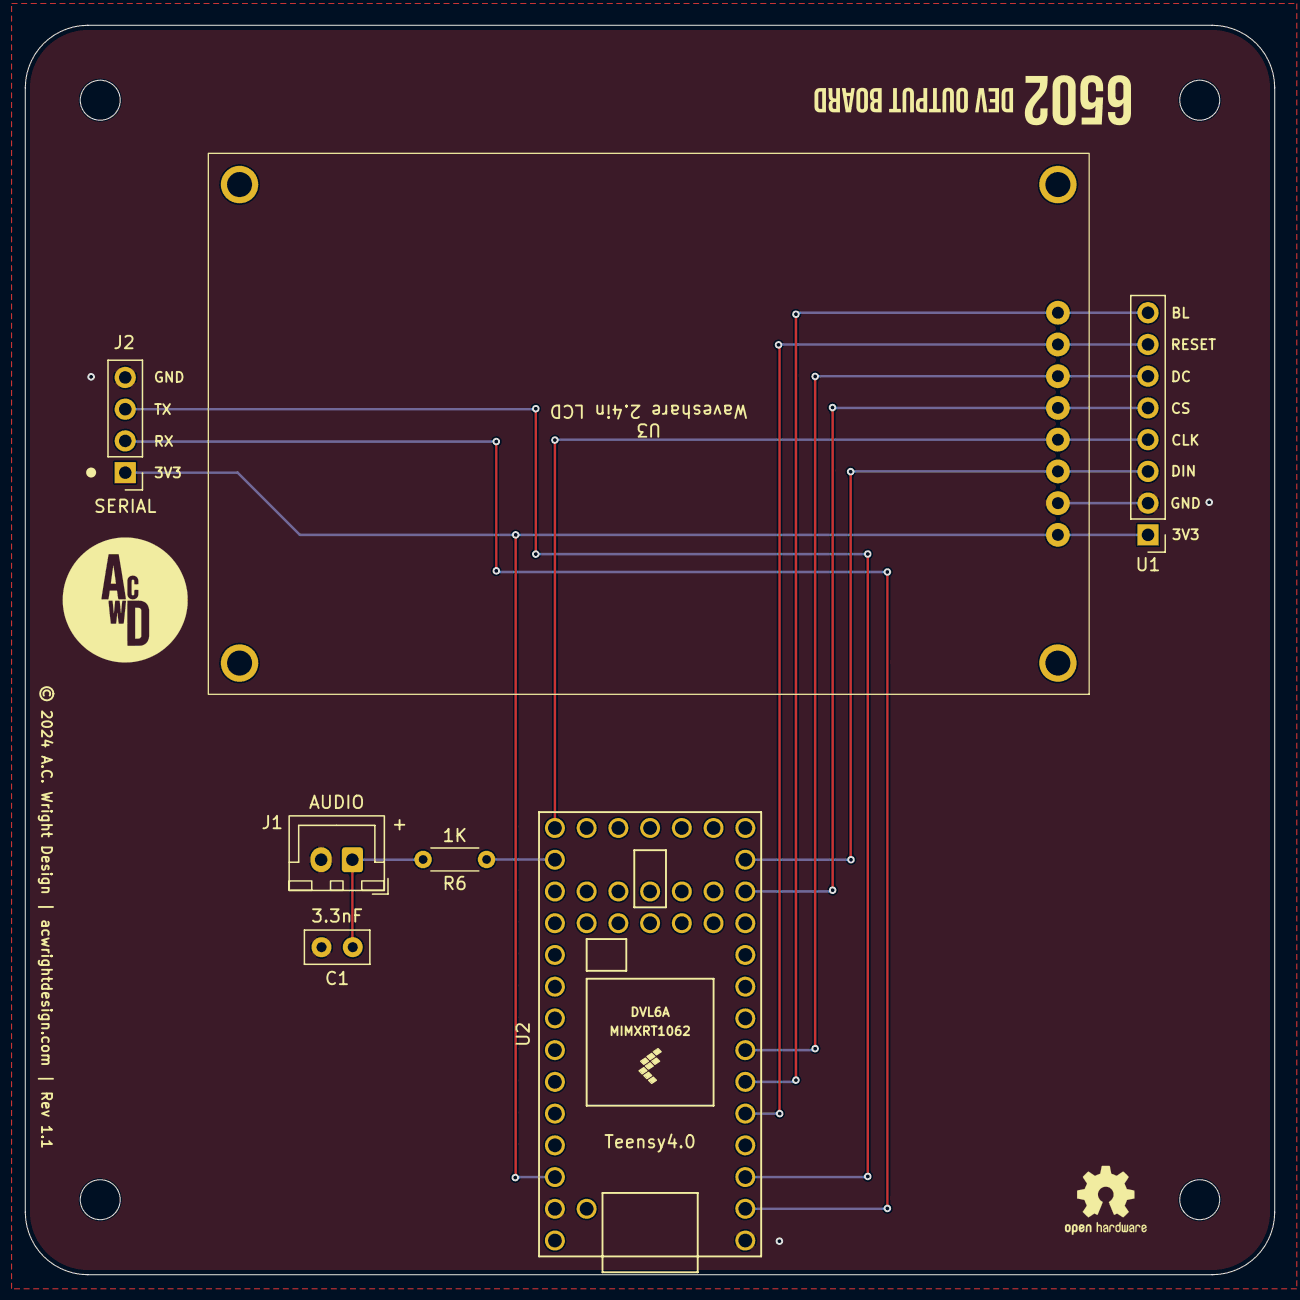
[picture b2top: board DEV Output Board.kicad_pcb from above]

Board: 2 copper layers, 100.0 x 100.0 mm, 11 parts (0 on the bottom side), 12 nets.

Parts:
C1: 3.3nF; C_Disc_D5.0mm_W2.5mm_P2.50mm
H1, H2, H3, H4: MountingHole; MountingHole_3.2mm_M3
J1: AUDIO; JST_XH_B2B-XH-A_1x02_P2.50mm_Vertical
J2: SERIAL; PinHeader_1x04_P2.54mm_Vertical
R6: 1K; R_Axial_DIN0204_L3.6mm_D1.6mm_P5.08mm_Horizontal
U1: Waveshare 2.4in LCD Header; PinHeader_1x08_P2.54mm_Vertical
U2: Teensy4.0; Teensy40
U3: Waveshare 2.4in LCD

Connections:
3V3: J2.1, U1.1 (VCC), U2.31 (3V3), U3.1 (VCC)
GND: C1.2, J1.2, J2.4, U1.2 (GND), U2.1 (GND), U2.32 (GND), U3.2 (GND)
LCD_BL: U1.8 (BL), U2.6 (4_BCLK2), U3.8 (BL)
LCD_CLK: U1.4 (CLK), U2.20 (13_SCK_CRX1_LED), U3.4 (CLK)
LCD_CS: U1.5 (CS), U2.12 (10_CS_MQSR), U3.5 (CS)
LCD_DATA: U1.3 (DIN), U2.13 (11_MOSI_CTX1), U3.3 (DIN)
LCD_DC: U1.6 (DC), U2.7 (5_IN2), U3.6 (DC)
LCD_RESET: U1.7 (RST), U2.5 (3_LRCLK2), U3.7 (RST)
unnamed: C1.1, J1.1, R6.2
RX: J2.2, U2.2 (0_RX1_CRX2_CS1)
SPEAKER: R6.1, U2.21 (14_A0_TX3_SPDIF_OUT)
TX: J2.3, U2.3 (1_TX1_CTX2_MISO1)

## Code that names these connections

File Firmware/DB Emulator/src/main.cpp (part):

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  pinMode(D6, INPUT);
  pinMode(D7, INPUT);

  pinMode(RESB, INPUT);
  pinMode(SYNC, INPUT);
  pinMode(RWB, INPUT);
  pinMode(PHI2, OUTPUT);
  digitalWrite(PHI2, HIGH);  // Set high to turn on onboard LED
  pinMode(IRQB, INPUT);
  pinMode(NMIB, INPUT);
  pinMode(RDY, INPUT);
  pinMode(BE, INPUT);

  // Switch inputs
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
#ifdef DEVBOARD_1
  pinMode(RESET_SWB, INPUT_PULLUP);
  pinMode(MOSI1, INPUT);
  pinMode(MISO1, INPUT);
  pinMode(SCK1, INPUT);
  pinMode(CS, INPUT);
#endif
}
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
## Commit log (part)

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2026-05-03 Cleanup DEV project
2026-05-04 Finish DEV cleanup
2026-05-04 Uppercase DEV
2026-05-04 Fix case-sensitive file and folder names (Dev -> DEV)
2026-05-16 Add BOMs
2026-05-19 Finish BOM and add to README
2026-05-19 Restore exclude from BOM
2026-05-24 Update Dev Output Board silkscreen
2026-06-11 README fix
2026-06-15 Change pull up resistor values
2026-06-16 Remove BOM CSV's
2026-06-18 Revert pull-up resistor value change

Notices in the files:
Firmware/DB Emulator/src/main.cpp:
© 2024 A.C. Wright Design |");
Hardware/DEV Board/Rev 1.0/DEV Board.kicad_pcb:
© 2024 A.C. Wright Design | acwrightdesign.com | Rev 1.0
Hardware/DEV Output Board/Rev 1.1/DEV Output Board.kicad_pcb:
© 2024 A.C. Wright Design | acwrightdesign.com | Rev 1.1
